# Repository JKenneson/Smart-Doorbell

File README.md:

# Senior Design ECE 1896
KFM Industries
Jonathan Kenneson, Alexander Furches, and Kyle Monto
Smart Doorbell

The following upper level directories can be found in the current directory:
* Arduino Testing
* Bluemix
* Eagle
* Checkoffs
* Libraries
* Solidworks

Each of the corresponding directories contains parts of the design project needed to recreate the final prototype.

The parts needed to recreate the prototype include:
* Arduino MEGA
* TTL Serial JPEG camera (Adafruit)
* PIR Motion Sensor
* ATWINC1500 Wifi breakout

The Arduino Testing directory contains files related to testing individual components and combinations of components.

The Bluemix directory contains code that can be imported in order to recreate the Node-RED setup associated with the project.

The Checkoff directory contains the code used during the checkoff demonstrations.

The Eagle directory contains all relevant files associated with development of the custom shield placed on top of the Arduino MEGA.

The Libraries directory contains the files associated with the libraries needed to run the Arduino code on the Arduino MEGA.

The Solidworks directory contains all files associated with the development of the 3D enclosure printed to house the final prototype.

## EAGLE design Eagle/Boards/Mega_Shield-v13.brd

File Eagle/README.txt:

This directory contains 3 subdirectories.

Boards - Contains the boards associated with the Arduino Mega and ATmega1284 MCP, and the final shield for the Arduino Mega.

Final Design Folder - Contains design files needed in order to have the custom components professionally printed.

Schematics - Contains the schematics for each of the MCPs examined as well as the Shield schematic that was ultimately choosen.

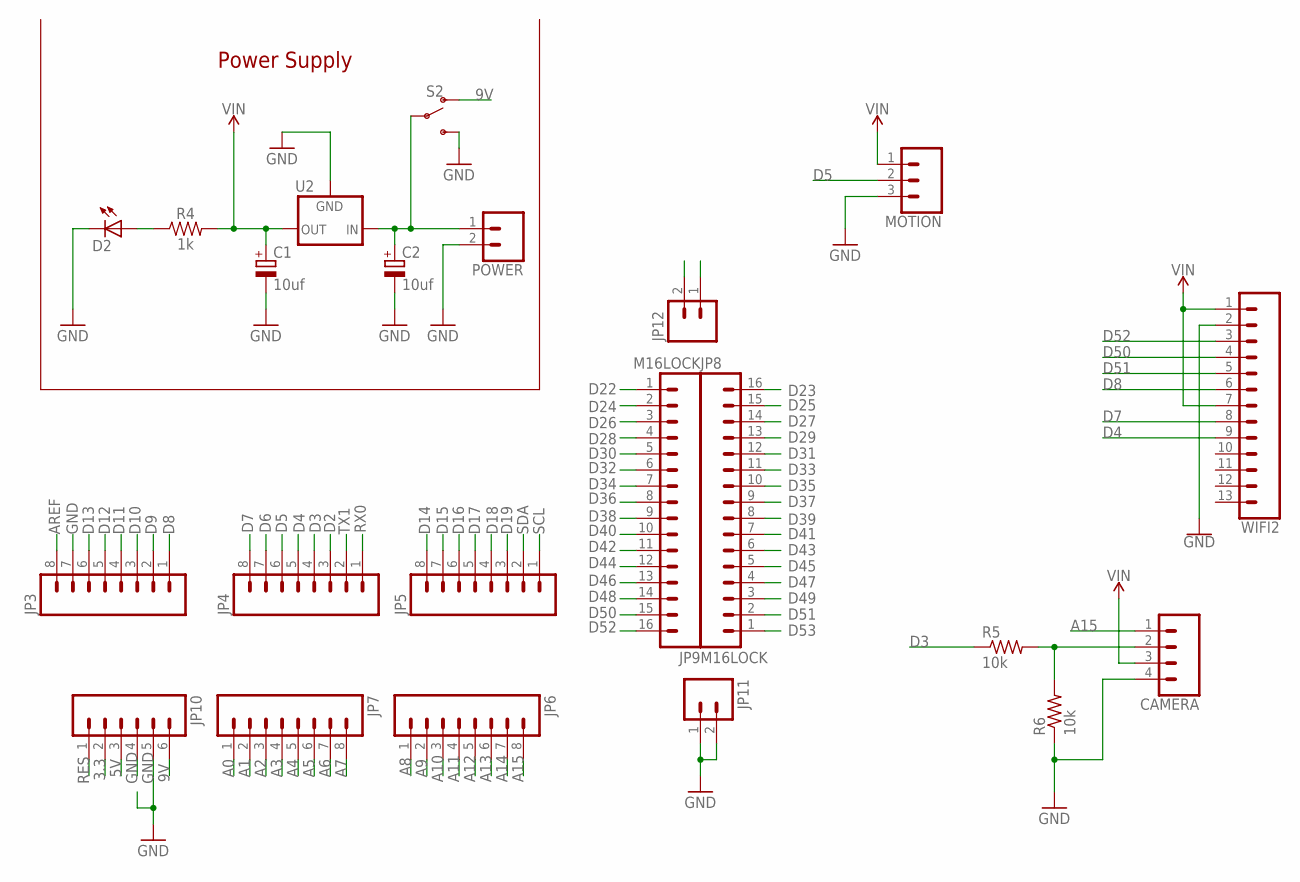
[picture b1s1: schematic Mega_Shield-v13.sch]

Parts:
C1, C2: 10uf; E2,5-6
CAMERA: CONN_04; 1X04
D2: LED3MM
JP3, JP4, JP5, JP6, JP7: M08LOCK; 1X08_LOCK
JP8, JP9: M16LOCK; 1X16_LOCK
JP10: M06LOCK; 1X06_LOCK
JP11, JP12: M02LOCK; 1X02_LOCK
MOTION: CONN_03; 1X03
POWER: CONN_025MM; SCREWTERMINAL-5MM-2
R4: 1k; AXIAL-0.3
R5, R6: 10k; 0207/10
S2: SWITCH-SPDT-PTH-11.6X4.0MM; SWITCH_SPDT_PTH_11.6X4.0MM
U2: V_REG_78XX-TO-220; TO-220-ALT
WIFI2: CONN_13; 1X13

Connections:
3.3: JP10.2
5V: JP10.3
5V@1: JP12.1, JP12.2
9V: JP10.6, S2.1 (O)
A0: JP7.1
A1: JP7.2
A2: JP7.3
A3: JP7.4
A4: JP7.5
A5: JP7.6
A6: JP7.7
A7: JP7.8
A8: JP6.1
A9: JP6.2
A10: JP6.3
A11: JP6.4
A12: JP6.5
A13: JP6.6
A14: JP6.7
A15: CAMERA.1, JP6.8
AREF: JP3.8
D2: JP4.3
D3: JP4.4, R5.1
D4: JP4.5, WIFI2.9
D5: JP4.6, MOTION.2
D6: JP4.7
D7: JP4.8, WIFI2.8
D8: JP3.1, WIFI2.6
D9: JP3.2
D10: JP3.3
D11: JP3.4
D12: JP3.5
D13: JP3.6
D14: JP5.8
D15: JP5.7
D16: JP5.6
D17: JP5.5
D18: JP5.4
D19: JP5.3
D22: JP9.1
D23: JP8.16
D24: JP9.2
D25: JP8.15
D26: JP9.3
D27: JP8.14
D28: JP9.4
D29: JP8.13
D30: JP9.5
D31: JP8.12
D32: JP9.6
D33: JP8.11
D34: JP9.7
D35: JP8.10
D36: JP9.8
D37: JP8.9
D38: JP9.9
D39: JP8.8
D40: JP9.10
D41: JP8.7
D42: JP9.11
D43: JP8.6
D44: JP9.12
D45: JP8.5
D46: JP9.13
D47: JP8.4
D48: JP9.14
D49: JP8.3
D50: JP9.15, WIFI2.4
D51: JP8.2, WIFI2.5
D52: JP9.16, WIFI2.3
D53: JP8.1
GND: C1.-, C2.-, CAMERA.4, D2.K (C), JP3.7, JP10.4, JP10.5, JP11.1, JP11.2, MOTION.3, POWER.2, R6.1, S2.3 (S), U2.GND, WIFI2.2
unnamed: C2.+, POWER.1, S2.2, U2.IN
unnamed: D2.A, R4.P$1 (1)
unnamed: CAMERA.2, R5.2, R6.2
RES: JP10.1
RX0: JP4.1
SCL: JP5.1
SDA: JP5.2
TX1: JP4.2
VIN: C1.+, CAMERA.3, MOTION.1, R4.P$2 (2), U2.OUT, WIFI2.1, WIFI2.7

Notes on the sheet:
Power Supply

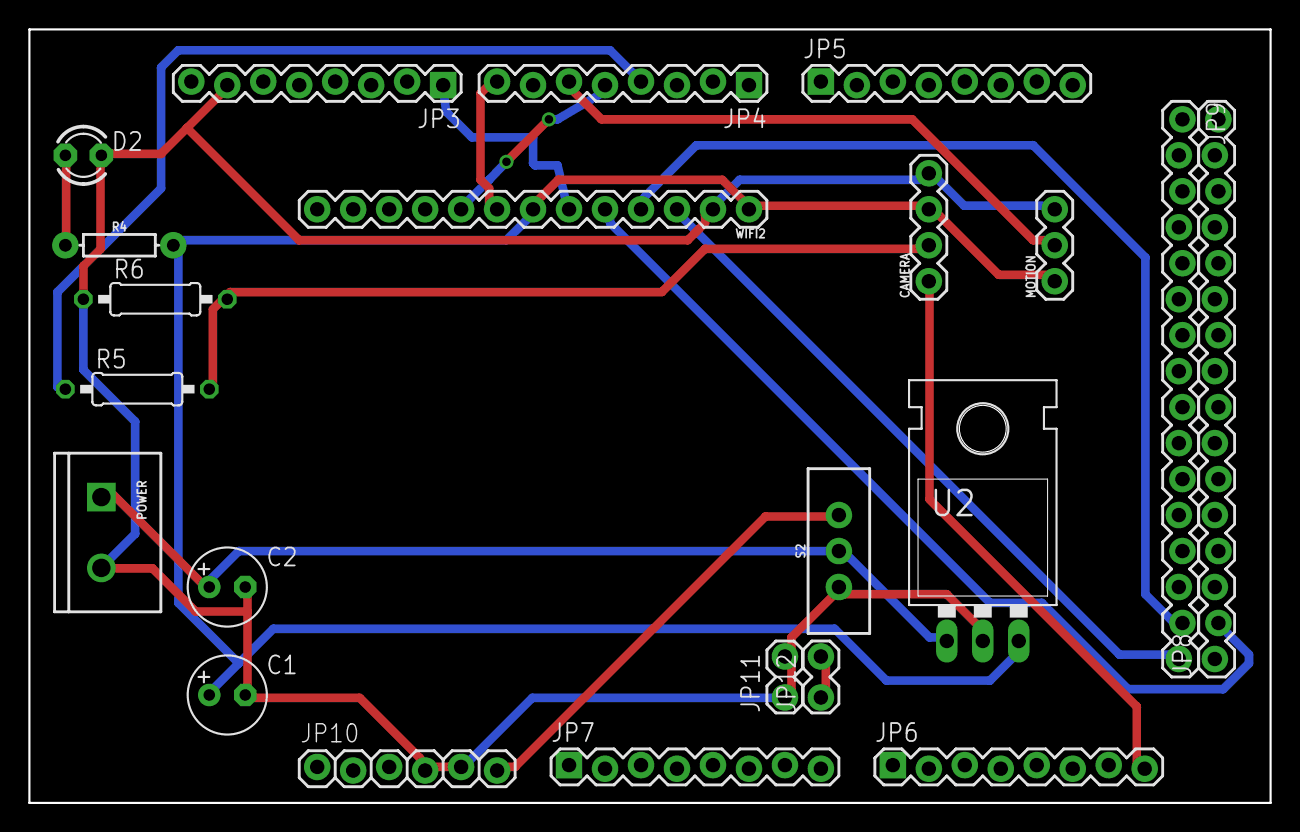
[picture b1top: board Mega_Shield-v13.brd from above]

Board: 2 copper layers, 87.6 x 54.6 mm, 22 parts (0 on the bottom side), 16 nets.

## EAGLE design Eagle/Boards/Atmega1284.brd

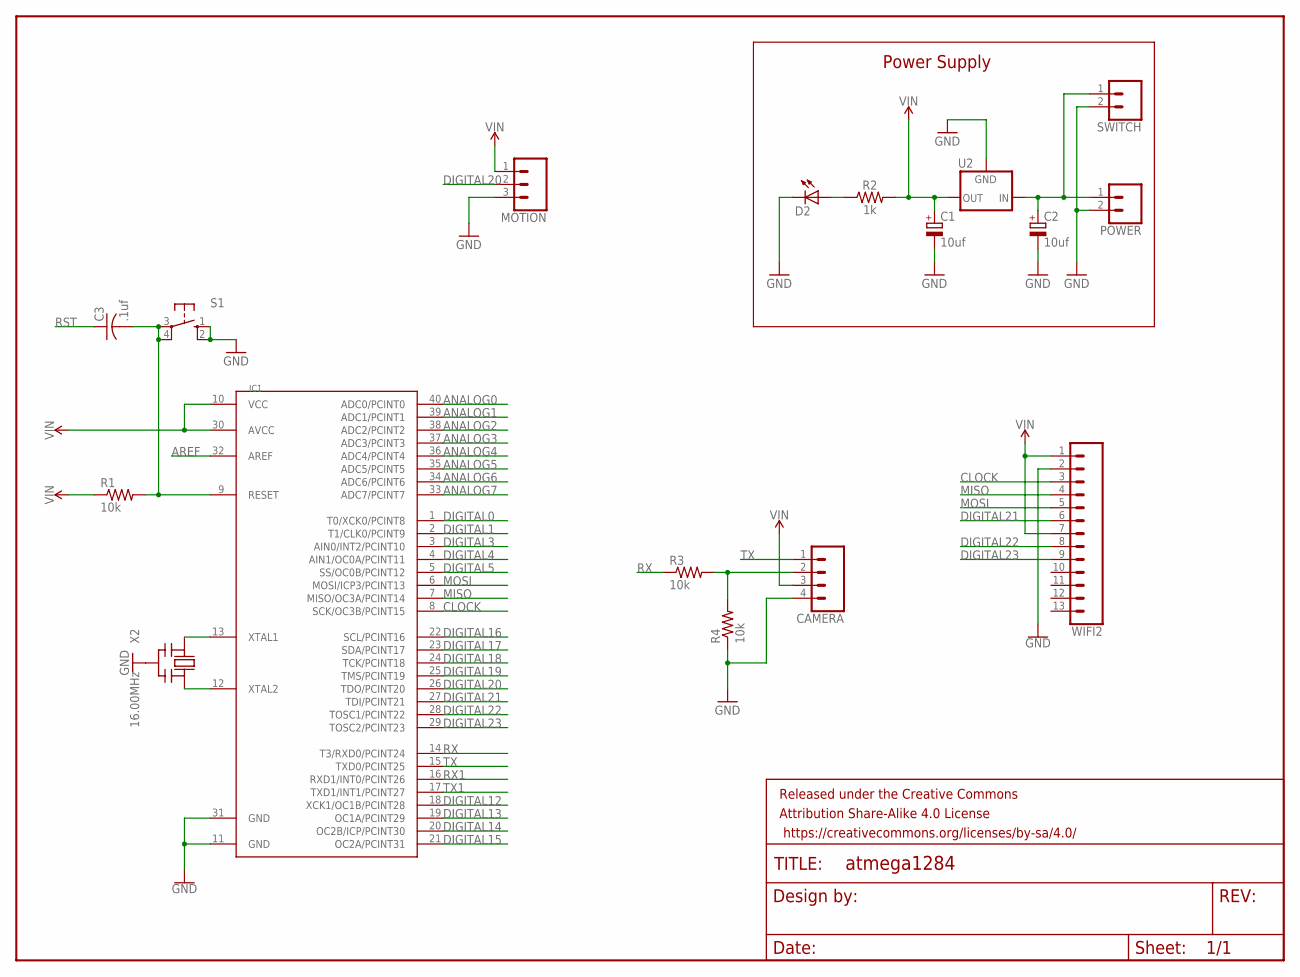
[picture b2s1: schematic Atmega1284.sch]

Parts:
C1, C2: 10uf; E2,5-6
C3: .1uf; C025-024X044
CAMERA: CONN_04; 1X04
D2: LED3MM
FRAME1: FRAME-LETTER; CREATIVE_COMMONS
IC1: MEGA1284P; DIL40
MOTION: CONN_03; 1X03
POWER: CONN_025MM; SCREWTERMINAL-5MM-2
R1, R3, R4: 10k; 0207/10
R2: 1k; AXIAL-0.3
S1: RESET; B3F-10XX
SWITCH: CONN_02; 1X02
U2: V_REG_78XX-TO-220; TO-220-ALT
WIFI2: CONN_13; 1X13
X2: 16.00MHz; CERM_OSC

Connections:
ANALOG0: IC1.40 (ADC0/PCINT0)
ANALOG1: IC1.39 (ADC1/PCINT1)
ANALOG2: IC1.38 (ADC2/PCINT2)
ANALOG3: IC1.37 (ADC3/PCINT3)
ANALOG4: IC1.36 (ADC4/PCINT4)
ANALOG5: IC1.35 (ADC5/PCINT5)
ANALOG6: IC1.34 (ADC6/PCINT6)
ANALOG7: IC1.33 (ADC7/PCINT7)
CLOCK: IC1.8 (SCK/OC3B/PCINT15), WIFI2.3
DIGITAL0: IC1.1 (T0/XCK0/PCINT8)
DIGITAL1: IC1.2 (T1/CLK0/PCINT9)
DIGITAL3: IC1.3 (AIN0/INT2/PCINT10)
DIGITAL4: IC1.4 (AIN1/OC0A/PCINT11)
DIGITAL5: IC1.5 (SS/OC0B/PCINT12)
DIGITAL12: IC1.18 (XCK1/OC1B/PCINT28)
DIGITAL13: IC1.19 (OC1A/PCINT29)
DIGITAL14: IC1.20 (OC2B/ICP/PCINT30)
DIGITAL15: IC1.21 (OC2A/PCINT31)
DIGITAL16: IC1.22 (SCL/PCINT16)
DIGITAL17: IC1.23 (SDA/PCINT17)
DIGITAL18: IC1.24 (TCK/PCINT18)
DIGITAL19: IC1.25 (TMS/PCINT19)
DIGITAL20: IC1.26 (TDO/PCINT20), MOTION.2
DIGITAL21: IC1.27 (TDI/PCINT21), WIFI2.6
DIGITAL22: IC1.28 (TOSC1/PCINT22), WIFI2.8
DIGITAL23: IC1.29 (TOSC2/PCINT23), WIFI2.9
GND: C1.-, C2.-, CAMERA.4, D2.K (C), IC1.11 (GND), MOTION.3, POWER.2, R4.1, S1.1 (S), S1.2 (S1), SWITCH.2, U2.GND, WIFI2.2, X2.P$2 (GND)
MISO: IC1.7 (MISO/OC3A/PCINT14), WIFI2.4
MOSI: IC1.6 (MOSI/ICP3/PCINT13), WIFI2.5
unnamed: C2.+, POWER.1, SWITCH.1, U2.IN
unnamed: D2.A, R2.P$1 (1)
unnamed: CAMERA.2, R3.2, R4.2
unnamed: IC1.13 (XTAL1), X2.P$1 (IN)
unnamed: IC1.12 (XTAL2), X2.P$3 (OUT)
RST: C3.1, C3.2, IC1.9 (RESET), R1.2, S1.3, S1.4 (P1)
RX: IC1.14 (T3/RXD0/PCINT24), R3.1
RX1: IC1.16 (RXD1/INT0/PCINT26)
TX: CAMERA.1, IC1.15 (TXD0/PCINT25)
TX1: IC1.17 (TXD1/INT1/PCINT27)
VIN: C1.+, CAMERA.3, IC1.10 (VCC), MOTION.1, R1.1, R2.P$2 (2), U2.OUT, WIFI2.1, WIFI2.7

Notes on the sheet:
Power Supply

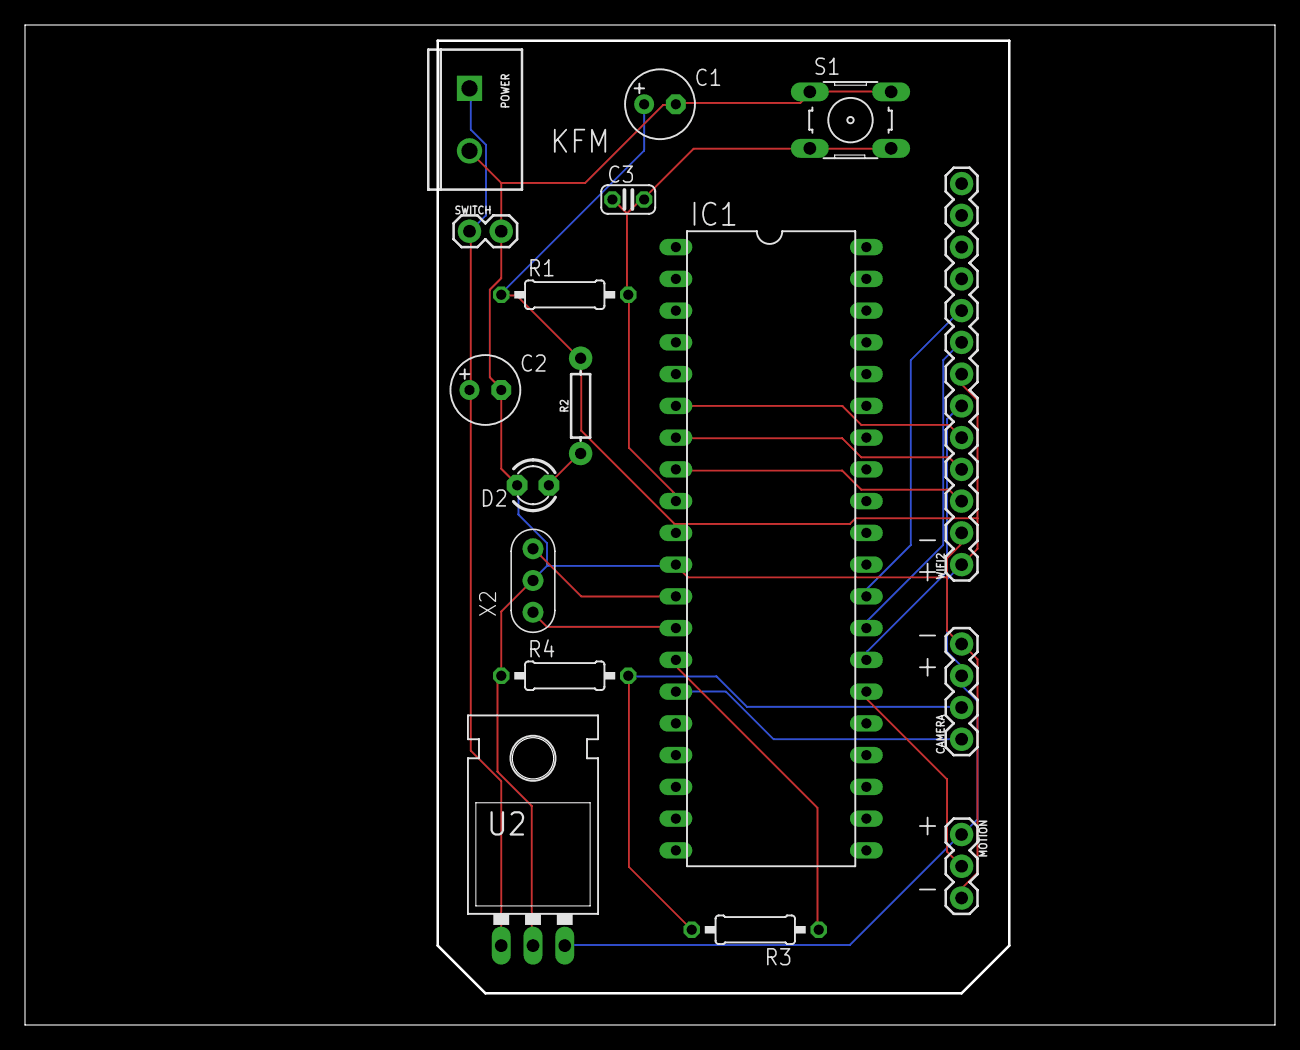
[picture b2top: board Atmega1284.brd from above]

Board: 2 copper layers, 99.8 x 79.8 mm, 18 parts (0 on the bottom side), 17 nets.

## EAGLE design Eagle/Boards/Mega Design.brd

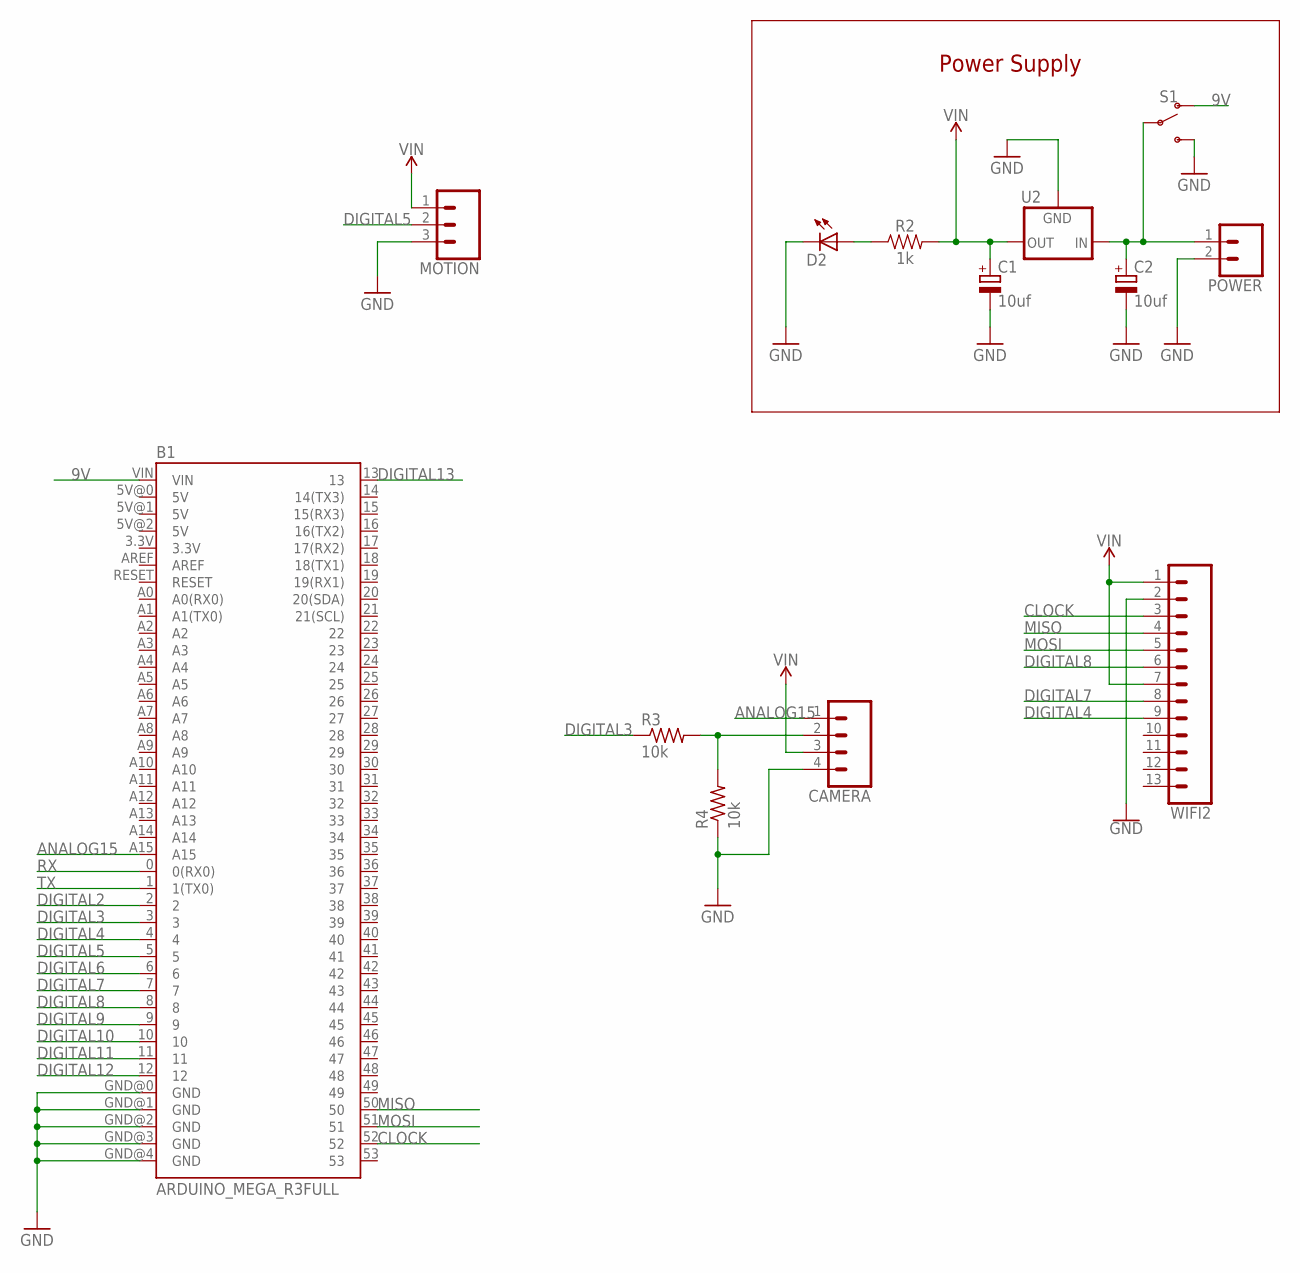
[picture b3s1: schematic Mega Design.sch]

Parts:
B1: ARDUINO_MEGA_R3FULL; ARDUINO_MEGA
C1, C2: 10uf; E2,5-6
CAMERA: CONN_04; 1X04
D2: LED3MM
MOTION: CONN_03; 1X03
POWER: CONN_025MM; SCREWTERMINAL-5MM-2
R2: 1k; AXIAL-0.3
R3, R4: 10k; 0207/10
S1: SWITCH-SPDT-PTH-11.6X4.0MM; SWITCH_SPDT_PTH_11.6X4.0MM
U2: V_REG_78XX-TO-220; TO-220-ALT
WIFI2: CONN_13; 1X13

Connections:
9V: B1.VIN, S1.1 (O)
ANALOG15: B1.A15, CAMERA.1
CLOCK: B1.52, WIFI2.3
DIGITAL2: B1.2
DIGITAL3: B1.3, R3.1
DIGITAL4: B1.4, WIFI2.9
DIGITAL5: B1.5, MOTION.2
DIGITAL6: B1.6
DIGITAL7: B1.7, WIFI2.8
DIGITAL8: B1.8, WIFI2.6
DIGITAL9: B1.9
DIGITAL10: B1.10
DIGITAL11: B1.11
DIGITAL12: B1.12
DIGITAL13: B1.13
GND: B1.GND@0 (GND), B1.GND@1 (GND), B1.GND@2 (GND), B1.GND@3 (GND), B1.GND@4 (GND), C1.-, C2.-, CAMERA.4, D2.K (C), MOTION.3, POWER.2, R4.1, S1.3 (S), U2.GND, WIFI2.2
MISO: B1.50, WIFI2.4
MOSI: B1.51, WIFI2.5
unnamed: C2.+, POWER.1, S1.2, U2.IN
unnamed: D2.A, R2.P$1 (1)
unnamed: CAMERA.2, R3.2, R4.2
RX: B1.0 (0(RX0))
TX: B1.1 (1(TX0))
VIN: C1.+, CAMERA.3, MOTION.1, R2.P$2 (2), U2.OUT, WIFI2.1, WIFI2.7

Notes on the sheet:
Power Supply

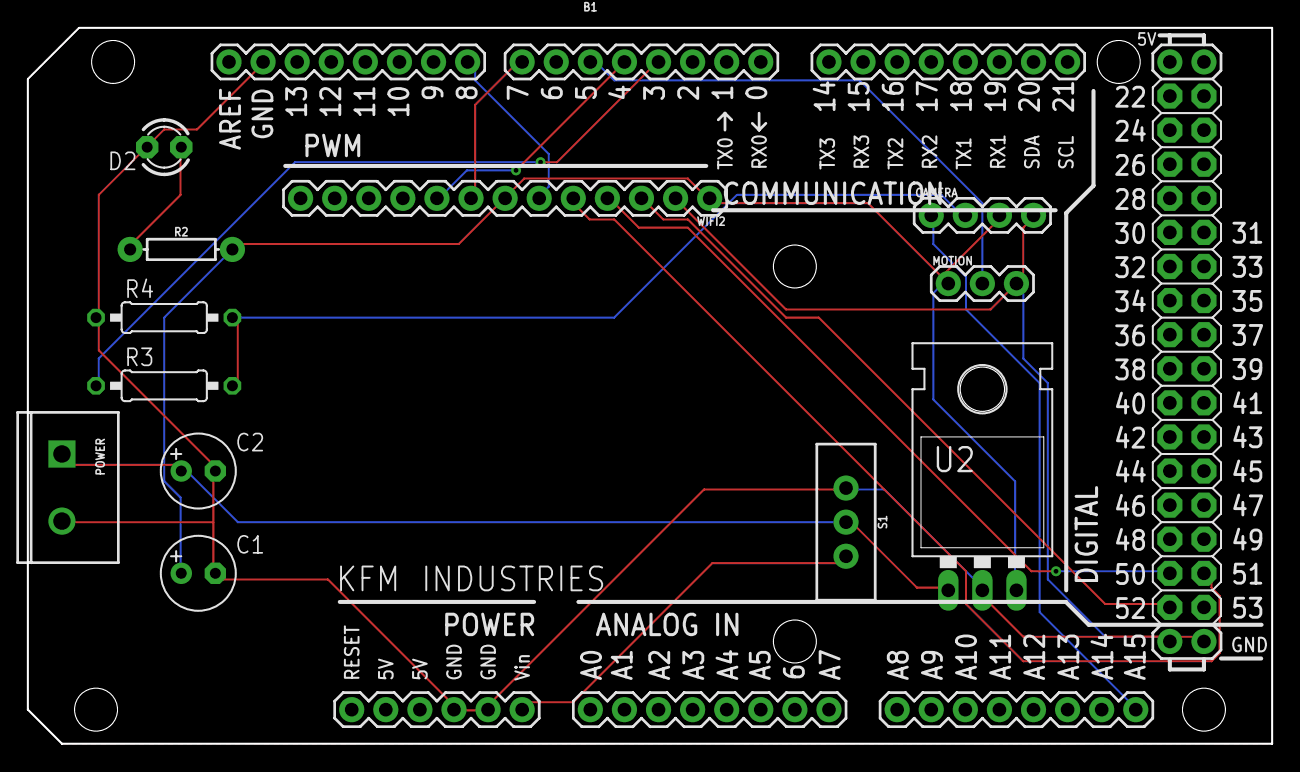
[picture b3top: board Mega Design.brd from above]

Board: 2 copper layers, 92.7 x 53.3 mm, 13 parts (0 on the bottom side), 15 nets.

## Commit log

2017-10-10 Simple PIR test
2017-10-11 Dump of Test code for camera
    test camera code dump
2017-10-11 Camera Test
2017-10-16 Wifi and Nodered testing
    Wifi testing and start of node red on IBM bluemix
2017-10-20 Created Demo1
    Demo 1 created for test using motion sensor and camera. Use
    TransmissionTest for transmission demo
2017-10-20 Addition of Camera Wiring reference
    Camera picture
2017-10-25 base64 images and Demo
    Addition of base64 test images and updated Demo1 and added
    Motion_Camera_Test for demo
2017-11-06 Demo2 working with Arduino Mega
2017-11-06 Camera Print to Serial as Hex
2017-11-08 Sending partial image data to IBM
2017-11-09 Complete picture sent to server (sometimes lost packets in transmission)
    Must look into how to fix dropped packets. However, it is now time for dinner
2017-11-09 Changing max packet size in library
2017-11-13 Updated MainFlow on Node Red
    Updated MainFlow on Node Red
2017-11-13 New wifi library
2017-11-14 Updated Main Flow of Node Red
    Updating Main Flow of Node Red to prep for transfer over to new IBM
    Bluemix account
2017-11-15 Small changes from demo
2017-11-17 Updated Main Flow - continuous flow
    No longer need to click link to evaluated image all done on upload,
    updated query and displays image details and email now in html format
2017-11-19 Compression with Demo 3
    Much faster data transfer speeds
2017-12-01 New Wifi
2017-12-02 Updated Node-RED flow and added READMEs
    READMEs added to Bluemix and libraries directory
2017-12-03 Directory structure change
2017-12-06 Added Board and Housing Files, updated README
2017-12-08 Addition of V2 top design

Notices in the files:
parts and their libraries:
SparkFun-Connectors: Licensing: Creative Commons ShareAlike 4.0 International - https://creativecommons.org/licenses/by-sa/4.0
SparkFun-Aesthetics: Released under the Creative Commons Attribution Share-Alike 4.0 License
SparkFun-Aesthetics: https://creativecommons.org/licenses/by-sa/4.0
